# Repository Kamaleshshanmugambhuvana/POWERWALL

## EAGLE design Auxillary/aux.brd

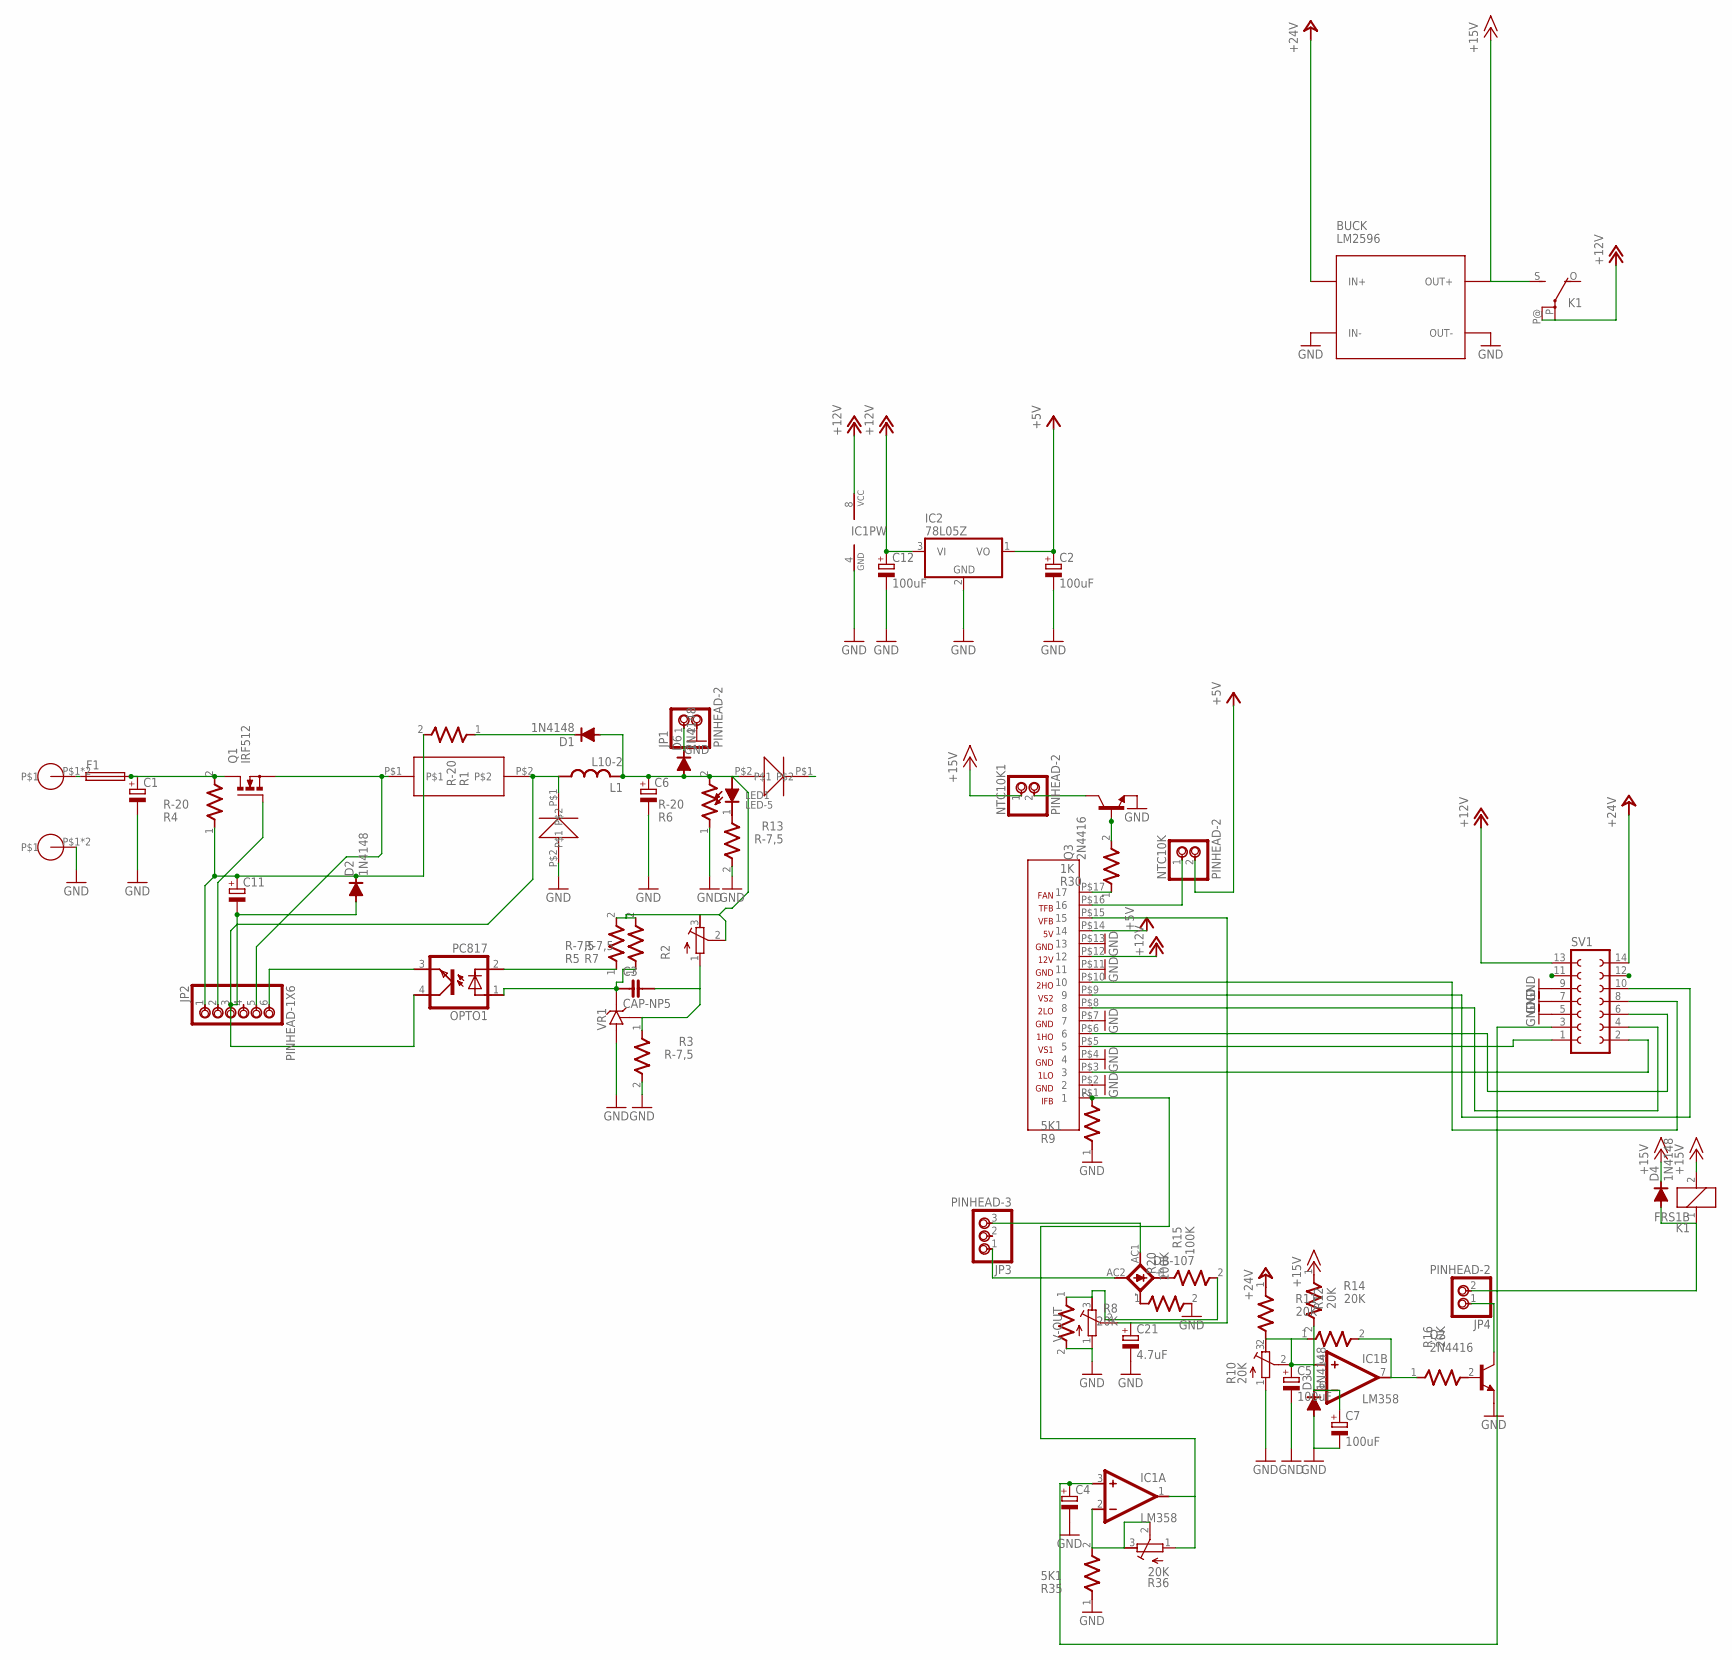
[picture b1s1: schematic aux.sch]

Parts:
BUCK: LM2596; DC-DC-STEP-DOWN-LM2596
C1, C6: CPOL-EUE7.5-18; E7,5-18
C2, C5, C7, C12: 100uF; E2,5-7
C3: CAP-NP5
C4: CPOL-EUE2.5-7; E2,5-7
C11: CPOL-EUE5-8.5; E5-8,5
C21: 4.7uF; E2,5-7
D1, D2, D3, D4, D6: 1N4148; D-7,5
DB-107: CAU-1A
F1: SH22
IC1: LM358; DIL-8
IC2: 78L05Z; TO92
JP1, JP4: PINHEAD-2
JP2: PINHEAD-1X6
JP3: PINHEAD-3
K1: FRS1B
L1: L10-2
LED1: LED-5; LED5
NTC10K, NTC10K1: PINHEAD-2
OPTO1: PC817; DIL-04
Q1: IRF512; TO220BV
Q2, Q3: 2N4416; TO92
R1, R4, R6: R-20
R2: R-TRIMM64W; RTRIM64W
R3, R5, R7, R13: R-7,5
R8, R11, R12, R14, R16: 20K; R-7,5
R9, R35: 5K1; R-7,5
R10, R36: 20K; RTRIM64W
R15, R20: 100K; R-7,5
R30: 1K; R-7,5
SV1: FE07-2
U$1, U$2: DSEI6060A
U$3, U$4: PIN5MM
U$5: SHUNT-0.01R
U$11: EGS002
V-OUT: R-TRIMM64W; RTRIM64W
VR1: TL431CLP; TO92-CLP

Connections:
+5V: C2.+, IC2.1 (VO), NTC10K.2, U$11.P$14 (14)
+12V: C12.+, IC1.8 (VCC), IC2.3 (VI), K1.P, K1.P@, SV1.13, U$11.P$12 (12)
+15V: BUCK.OUT+, D4.C, K1.2, K1.S, NTC10K1.1, R14.1
+24V: BUCK.IN+, R11.1, SV1.14
GND: BUCK.IN-, BUCK.OUT-, C1.-, C2.-, C4.-, C5.-, C6.-, C7.-, C12.-, C21.-, D3.A, IC1.4 (GND), IC2.2 (GND), JP1.2, Q2.3 (E), Q3.3 (E), R3.2, R6.1, R8.2, R9.1, R10.1 (A), R13.2, R20.2, R35.1, SV1.5, SV1.7, SV1.9, U$1.P$2, U$3.P$1, U$3.P$2, U$11.P$2 (2), U$11.P$4 (4), U$11.P$7 (7), U$11.P$11 (11), U$11.P$13 (13), V-OUT.1 (A), VR1.A
unnamed: F1.1, U$4.P$1, U$4.P$2
unnamed: JP2.2, Q1.G
unnamed: D1.C, R1.1
unnamed: LED1.K, R13.1
unnamed: C5.+, IC1.5 (+IN), R10.2 (S), R10.3 (E), R11.2, R12.1
unnamed: OPTO1.2 (C), R5.1
unnamed: C4.+, IC1.3 (+IN), SV1.3
unnamed: C11.+, D2.C, JP2.1, R1.2 (3), R4.1
unnamed: C3.2, R2.1 (A), R3.1, VR1.R
unnamed: SV1.2, U$11.P$3 (3)
unnamed: JP2.5, Q1.S, U$5.P$1
unnamed: C1.+, F1.2, Q1.D, R4.2 (3)
unnamed: C3.1, OPTO1.1 (A), R7.1, VR1.C
unnamed: C6.+, D1.A, D6.A, L1.P$3 (2), L1.P$4 (2), LED1.A, R2.2 (S), R2.3 (E), R5.2, R6.2 (3), R7.2, U$2.P$2
unnamed: R8.1, R15.2, V-OUT.3 (E)
unnamed: SV1.6, U$11.P$6 (6)
unnamed: D6.C, JP1.1
unnamed: SV1.4, U$11.P$8 (8)
unnamed: IC1.2 (-IN), R35.2, R36.2 (S), R36.3 (E)
unnamed: SV1.10, U$11.P$9 (9)
unnamed: SV1.8, U$11.P$10 (10)
unnamed: R30.1, U$11.P$17 (17)
unnamed: DB-107.AC2 (-), JP3.1
unnamed: IC1.7 (OUT), R12.2, R16.1
unnamed: C7.+, D3.C, IC1.6 (-IN), R14.2
unnamed: C11.-, D2.A, JP2.3, L1.P$1 (1), L1.P$2 (1), OPTO1.4 (COL), U$1.P$1, U$5.P$2
unnamed: Q2.2 (B), R16.2
unnamed: JP4.1, Q2.1 (C)
unnamed: D4.A, JP4.2, K1.1
unnamed: SV1.1, U$11.P$5 (5)
unnamed: JP2.6, OPTO1.3 (EMI)
unnamed: Q3.2 (B), R30.2
unnamed: C21.+, U$11.P$15 (15), V-OUT.2 (S)
unnamed: NTC10K1.2, Q3.1 (C)
unnamed: DB-107.+, R15.1
unnamed: DB-107.- (AC2), R20.1
unnamed: NTC10K.1, U$11.P$16 (16)
unnamed: IC1.1 (OUT), R9.2, R36.1 (A), U$11.P$1 (1)
unnamed: DB-107.AC1, JP3.3
VCC: U$2.P$1

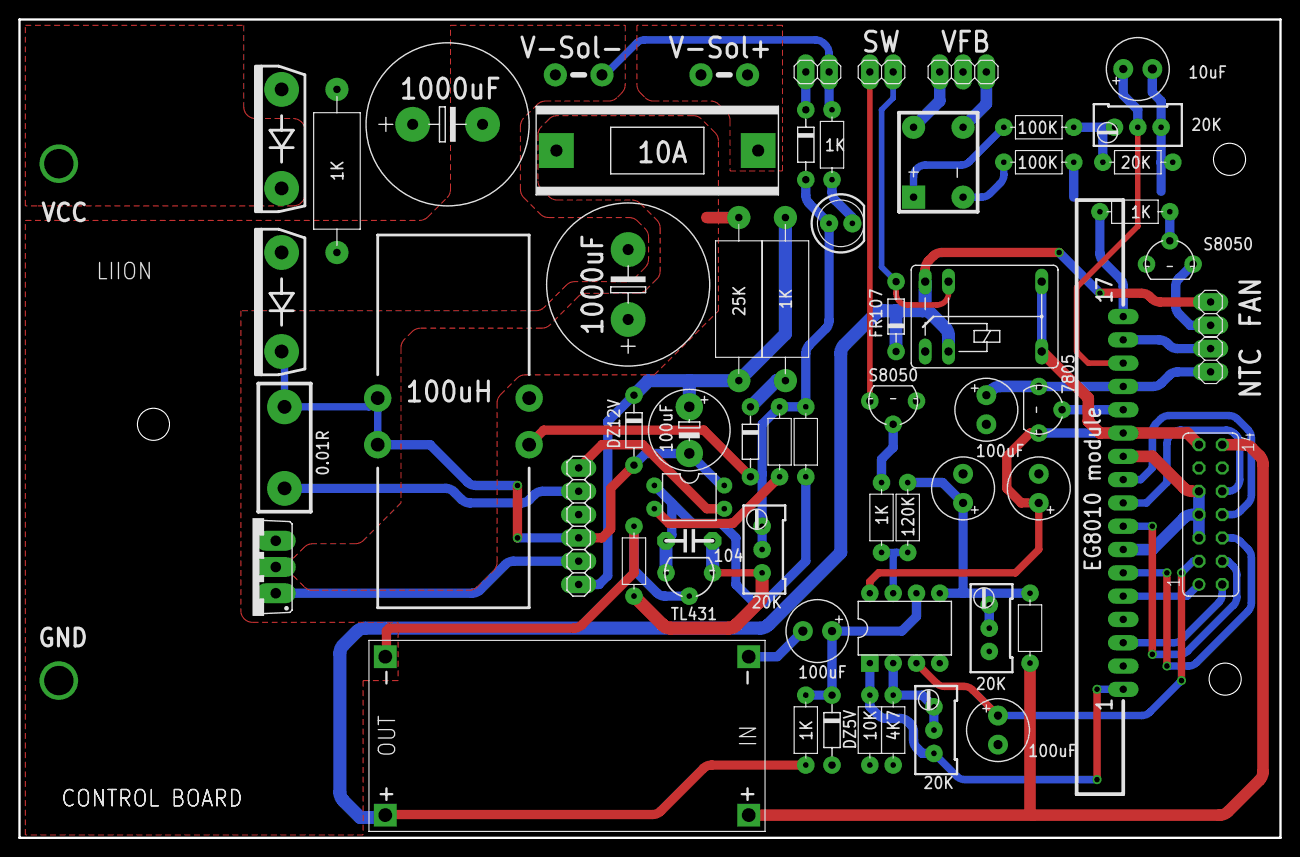
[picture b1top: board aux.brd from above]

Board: 2 copper layers, 137.5 x 89.2 mm, 62 parts (0 on the bottom side), 44 nets.

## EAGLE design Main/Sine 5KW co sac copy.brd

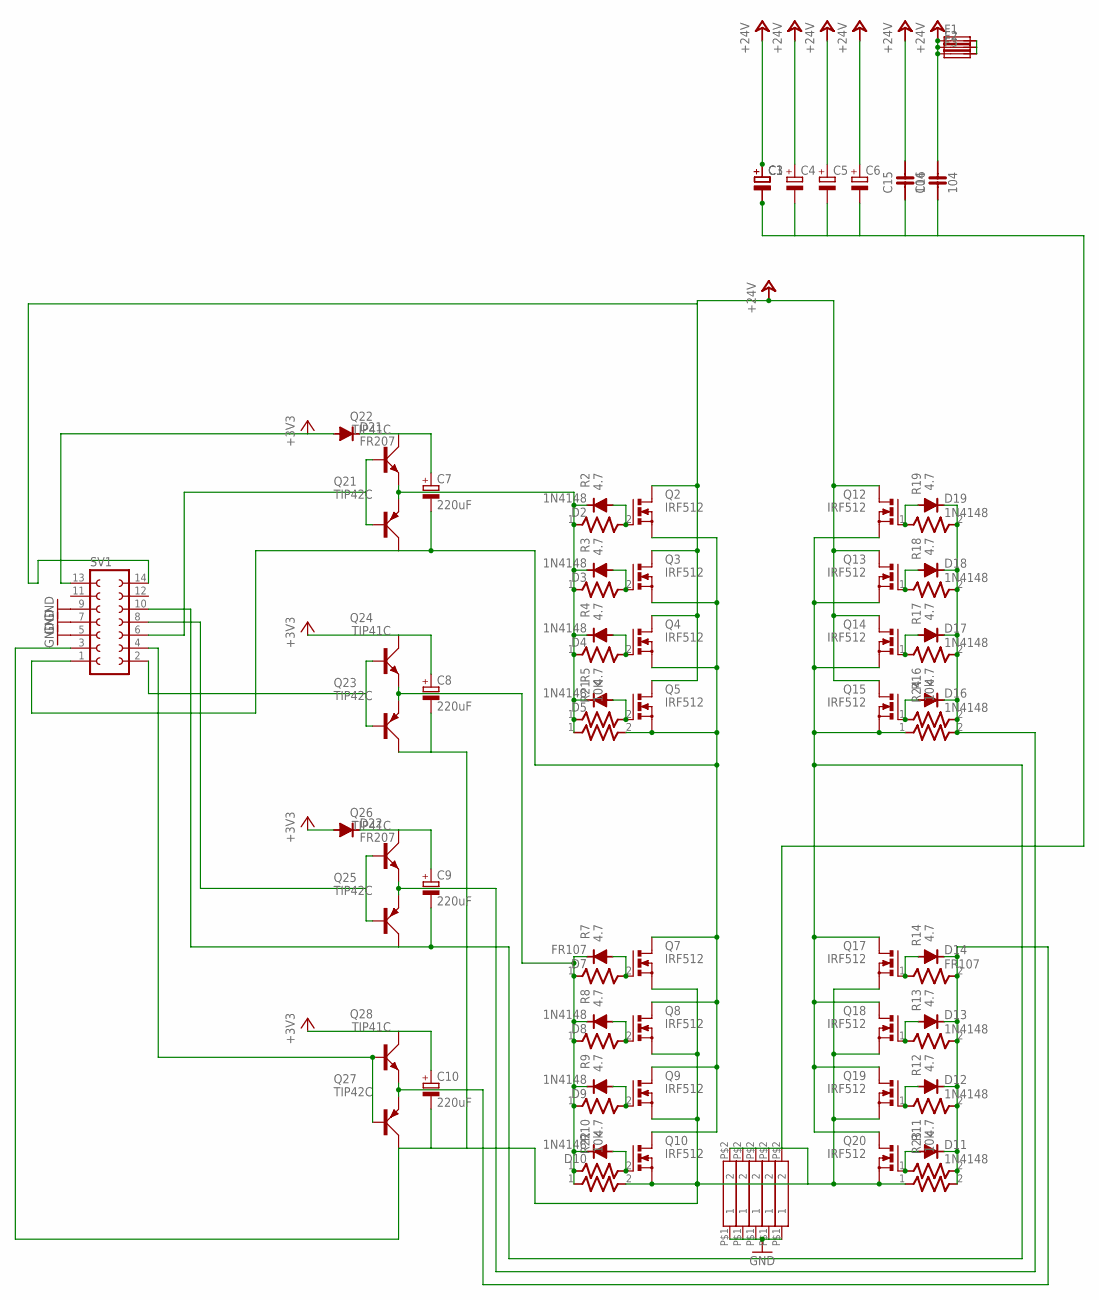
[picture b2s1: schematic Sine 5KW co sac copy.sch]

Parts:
C1, C3, C4, C5, C6: CPOL-EUE7.5-18; E7,5-18
C7, C8, C9, C10: 220uF; E5-8,5
C15, C16: 104; CAP-NP5
D2, D3, D4, D5, D8, D9, D10, D11, D12, D13, D16, D17, D18, D19: 1N4148; D-7,5
D7, D14: FR107; D-7,5
D21, D22: FR207; D-7,5
F1, F2, F3: LITTLEFUSE
Q2, Q3, Q4, Q5, Q7, Q8, Q9, Q10, Q12, Q13, Q14, Q15, Q17, Q18, Q19, Q20: IRF512; TO220BV
Q21, Q23, Q25, Q27: TIP42C; TO220AV
Q22, Q24, Q26, Q28: TIP41C; TO220AV
R2, R3, R4, R5, R7, R8, R9, R10, R11, R12, R13, R14, R16, R17, R18, R19: 4.7; R-7,5
R21: 10K; R-7,5
R22, R23, R24: 10k; R-7,5
SV1: FE07-2
U$2, U$3, U$8, U$9, U$10: SHUNT

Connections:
+3V3: C8.+, C10.+, D21.A, D22.A, Q24.C, Q28.C, SV1.13
GND: SV1.5, SV1.7, SV1.9, U$2.P$1 (1), U$3.P$1 (1), U$8.P$1 (1), U$9.P$1 (1), U$10.P$1 (1)
unnamed: Q23.B, Q24.B, SV1.2
unnamed: C9.+, D22.C, Q26.C
unnamed: Q21.B, Q22.B, SV1.6
unnamed: D7.C, D8.C, D9.C, D10.C, Q23.E, Q24.E, R7.1, R8.1, R9.1, R10.1, R22.1
unnamed: D13.A, Q18.G, R13.1
unnamed: Q27.B, Q28.B, SV1.4
unnamed: D2.A, Q2.G, R2.2
unnamed: D3.A, Q3.G, R3.2
unnamed: D4.A, Q4.G, R4.2
unnamed: D5.A, Q5.G, R5.2
unnamed: F1.2, F2.2, F3.2
unnamed: D7.A, Q7.G, R7.2
unnamed: D8.A, Q8.G, R8.2
unnamed: D9.A, Q9.G, R9.2
unnamed: D10.A, Q10.G, R10.2
unnamed: D11.A, Q20.G, R11.1
unnamed: D12.A, Q19.G, R12.1
unnamed: C9.-, Q12.S, Q13.S, Q14.S, Q15.S, Q17.D, Q18.D, Q19.D, Q20.D, Q25.C, R24.1, SV1.10
unnamed: D16.A, Q15.G, R16.1
unnamed: D17.A, Q14.G, R17.1
unnamed: D18.A, Q13.G, R18.1
unnamed: D19.A, Q12.G, R19.1
unnamed: Q25.B, Q26.B, SV1.8
unnamed: D14.A, Q17.G, R14.1
unnamed: C1.-, C3.-, C4.-, C5.-, C6.-, C8.-, C10.-, C15.1, C16.1, Q7.S, Q8.S, Q9.S, Q10.S, Q17.S, Q18.S, Q19.S, Q20.S, Q23.C, Q27.C, R22.2, R23.1, SV1.3, U$2.P$2 (2), U$3.P$2 (2), U$8.P$2 (2), U$9.P$2 (2), U$10.P$2 (2)
unnamed: D11.C, D12.C, D13.C, D14.C, Q27.E, Q28.E, R11.2, R12.2, R13.2, R14.2, R23.2
unnamed: D16.C, D17.C, D18.C, D19.C, Q25.E, Q26.E, R16.2, R17.2, R18.2, R19.2, R24.2
unnamed: C7.-, Q2.S, Q3.S, Q4.S, Q5.S, Q7.D, Q8.D, Q9.D, Q10.D, Q21.C, R21.2, SV1.1
unnamed: C7.+, D21.C, Q22.C
unnamed: D2.C, D3.C, D4.C, D5.C, Q21.E, Q22.E, R2.1, R3.1, R4.1, R5.1, R21.1
VCC: C1.+, C3.+, C4.+, C5.+, C6.+, C15.2, C16.2, F1.1, F2.1, F3.1, Q2.D, Q3.D, Q4.D, Q5.D, Q12.D, Q13.D, Q14.D, Q15.D, SV1.14

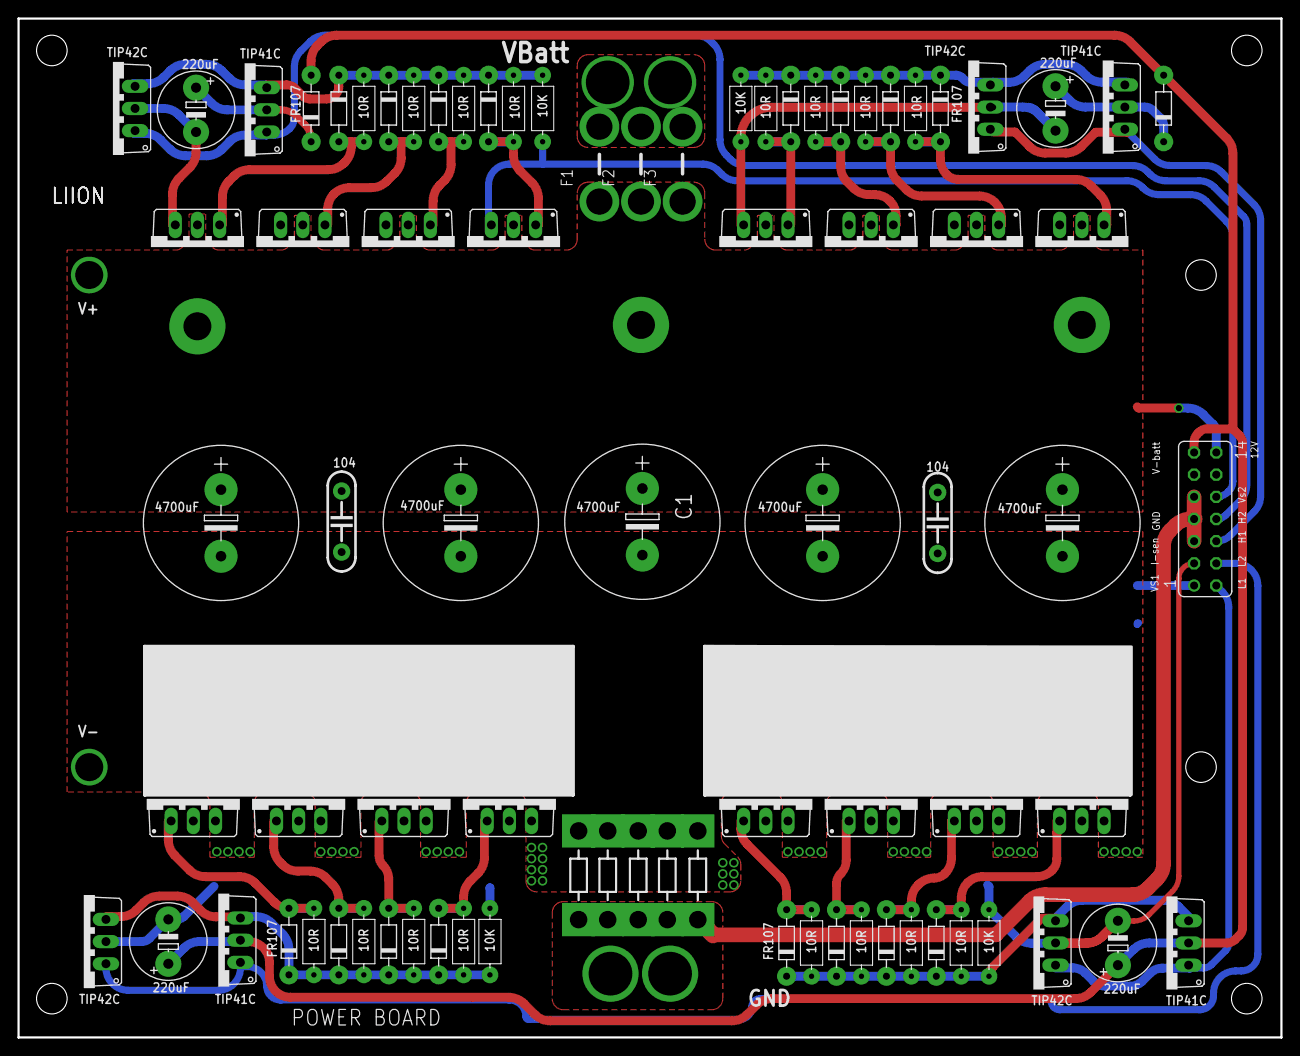
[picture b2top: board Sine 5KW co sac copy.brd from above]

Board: 2 copper layers, 144.6 x 116.7 mm, 82 parts (0 on the bottom side), 33 nets.

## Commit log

2024-10-17 Add files via upload
    PCB Board files designed on autodesk Eagle and battery 3D model design

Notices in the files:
parts and their libraries:
diy-modules: Released under the Creative Commons Attribution 4.0 International License: http://creativecommons.org/licenses/by/4.0
